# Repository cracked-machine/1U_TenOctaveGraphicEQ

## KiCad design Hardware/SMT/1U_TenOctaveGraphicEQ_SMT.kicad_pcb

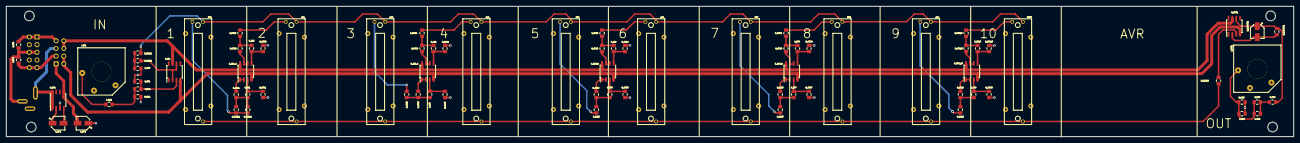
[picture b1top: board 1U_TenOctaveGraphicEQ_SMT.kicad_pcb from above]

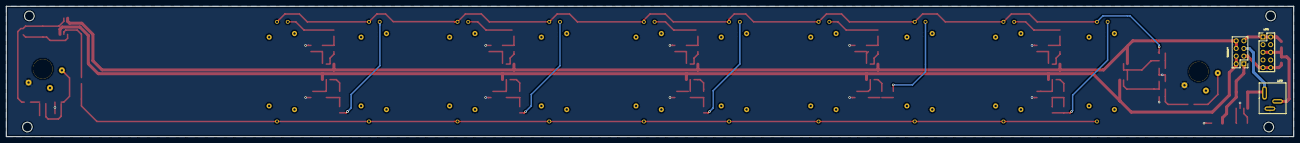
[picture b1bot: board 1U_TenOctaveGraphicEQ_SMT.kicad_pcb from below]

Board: 2 copper layers, 426.7 x 43.2 mm, 83 parts (3 on the bottom side), 62 nets.

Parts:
C_BP1, C_BP2: 100nF; C_0805_2012Metric_Pad1.15x1.40mm_HandSolder
C_BUFOUT1: 100uF; CP_Elec_4x5.4
C_CP1, C_CP2: 10uF; CP_Elec_4x5.4
C_DC1: 470nF; C_0805_2012Metric_Pad1.15x1.40mm_HandSolder
C_DC2, C_DC3: 1uF; C_0805_2012Metric_Pad1.15x1.40mm_HandSolder
C_GY1: 220nF; C_0805_2012Metric_Pad1.15x1.40mm_HandSolder
C_GY2: 100nF; C_0805_2012Metric_Pad1.15x1.40mm_HandSolder
C_GY3: 68nF; C_0805_2012Metric_Pad1.15x1.40mm_HandSolder
C_GY4: 33nF; C_0805_2012Metric_Pad1.15x1.40mm_HandSolder
C_GY5: 15nF; C_0805_2012Metric_Pad1.15x1.40mm_HandSolder
C_GY6: 10nF; C_0805_2012Metric_Pad1.15x1.40mm_HandSolder
C_GY7: 4.7nF; C_0805_2012Metric_Pad1.15x1.40mm_HandSolder
C_GY8: 2.2nF; C_0805_2012Metric_Pad1.15x1.40mm_HandSolder
C_GY9: 1nF; C_0805_2012Metric_Pad1.15x1.40mm_HandSolder
C_GY10: 680pF; C_0805_2012Metric_Pad1.15x1.40mm_HandSolder
C_PRE2: 1uF; C_0805_2012Metric_Pad1.15x1.40mm_HandSolder
C_PRE3: 390nF; C_0805_2012Metric_Pad1.15x1.40mm_HandSolder
C_PRE4: 220nF; C_0805_2012Metric_Pad1.15x1.40mm_HandSolder
C_PRE5: 100nF; C_0805_2012Metric_Pad1.15x1.40mm_HandSolder
C_PRE6: 47nF; C_0805_2012Metric_Pad1.15x1.40mm_HandSolder
C_PRE7: 22nF; C_0805_2012Metric_Pad1.15x1.40mm_HandSolder
C_PRE8: 10nF; C_0805_2012Metric_Pad1.15x1.40mm_HandSolder
C_PRE9: 6.8nF; C_0805_2012Metric_Pad1.15x1.40mm_HandSolder
C_PRE10: 3.3nF; C_0805_2012Metric_Pad1.15x1.40mm_HandSolder
C_PREA1: 680nF; C_0805_2012Metric_Pad1.15x1.40mm_HandSolder
C_PREB1: 820nF; C_0805_2012Metric_Pad1.15x1.40mm_HandSolder
C_RF1, C_RF2: 100pF; C_0805_2012Metric_Pad1.15x1.40mm_HandSolder
C_RF3: 1nF; C_0805_2012Metric_Pad1.15x1.40mm_HandSolder
J_IN1: AudioJack2_Ground_Switch; 112APCX
J_OUT1: AudioJack2_Ground_Switch; 112APCX
J_PS1: Conn_02x05_Odd_Even; PinHeader_2x05_P2.54mm_Vertical
J_PS2: Barrel_Jack; Wurth Elektronik Through Hole DC Power Socket WR-DC Series,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
J_PWRSEL1: Conn_02x04_Odd_Even; PinHeader_2x04_P2.54mm_Vertical
RV1, RV2, RV3, RV4, RV5, RV6, RV7, RV8, RV9, RV10: 10K; PTA2043
R_BEAD1, R_BEAD2: 10R; R_0805_2012Metric_Pad1.15x1.40mm_HandSolder
R_BUFOUT1: 2K7; R_0805_2012Metric_Pad1.15x1.40mm_HandSolder
R_GAIN1: 2K7; R_0805_2012Metric_Pad1.15x1.40mm_HandSolder
R_GYA1, R_GYA2, R_GYA3, R_GYA4, R_GYA5, R_GYA6, R_GYA7, R_GYA8, R_GYA9, R_GYA10: 680R; R_0805_2012Metric_Pad1.15x1.40mm_HandSolder
R_GYB1, R_GYB8: 110K; R_0805_2012Metric_Pad1.15x1.40mm_HandSolder
R_GYB2, R_GYB5: 100K; R_0805_2012Metric_Pad1.15x1.40mm_HandSolder
R_GYB3, R_GYB7: 91K; R_0805_2012Metric_Pad1.15x1.40mm_HandSolder
R_GYB4, R_GYB6, R_GYB9: 82K; R_0805_2012Metric_Pad1.15x1.40mm_HandSolder
R_GYB10: 62K; R_0805_2012Metric_Pad1.15x1.40mm_HandSolder
R_PD1: 100K; R_0805_2012Metric_Pad1.15x1.40mm_HandSolder
R_PD2: 1M; R_0805_2012Metric_Pad1.15x1.40mm_HandSolder
R_RF1: 1K; R_0805_2012Metric_Pad1.15x1.40mm_HandSolder
R_RF2: 470R; R_0805_2012Metric_Pad1.15x1.40mm_HandSolder
U_CP1: _TC7662B; SOIC-8_3.9x4.9mm_P1.27mm
U_GY1_2, U_GY3_4, U_GY5_6, U_GY7_8, U_GY9_10: TL072; SOIC-8_3.9x4.9mm_P1.27mm
U_IN1: TL071; SOIC-8_3.9x4.9mm_P1.27mm
U_OUT1: TL071; SOIC-8_3.9x4.9mm_P1.27mm

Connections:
/CP_V+: J_PS2.1, J_PWRSEL1.5, U_CP1.1, U_CP1.8
/CP_V-: C_CP2.2, J_PWRSEL1.1, U_CP1.5
/EURO_GND: C_BP1.2, C_BP2.1, J_PS1.5, J_PS1.6, J_PS2.3
/GND: C_CP2.1, C_RF1.2, C_RF2.2, C_RF3.2, J_IN1.S, J_OUT1.S, J_PS2.2, R_GYB1.2, R_GYB2.2, R_GYB3.2, R_GYB4.2, R_GYB5.2, R_GYB6.2, R_GYB7.2, R_GYB8.2, R_GYB9.2, R_GYB10.2, R_PD1.2, R_PD2.2, U_CP1.3
/PS_V+: C_BP1.1, J_PS1.1, J_PS1.2, J_PWRSEL1.7
/PS_V-: C_BP2.2, J_PS1.9, J_PS1.10, J_PWRSEL1.3
/SeriesResonatorBlock/EQ_IN: RV1.1, RV2.1, RV3.1, RV4.1, RV5.1, RV6.1, RV7.1, RV8.1, RV9.1, RV10.1, R_BEAD1.1
/SeriesResonatorBlock/EQ_OUT: RV1.3, RV2.3, RV3.3, RV4.3, RV5.3, RV6.3, RV7.3, RV8.3, RV9.3, RV10.3, R_BEAD2.2
/V+: J_PWRSEL1.6, J_PWRSEL1.8, U_GY1_2.8, U_GY3_4.8, U_GY5_6.8, U_GY7_8.8, U_GY9_10.8, U_IN1.7, U_OUT1.7
/V-: J_PWRSEL1.2, J_PWRSEL1.4, U_GY1_2.4, U_GY3_4.4, U_GY5_6.4, U_GY7_8.4, U_GY9_10.4, U_IN1.4, U_OUT1.4
unnamed: C_BUFOUT1.1, R_BUFOUT1.1, R_RF2.2, U_OUT1.6
unnamed: C_BUFOUT1.2, R_BUFOUT1.2, U_OUT1.2
unnamed: C_CP1.1, U_CP1.2
unnamed: C_CP1.2, U_CP1.4
unnamed: C_DC1.1, R_PD1.1, R_RF1.1
unnamed: C_DC1.2, J_IN1.T
unnamed: C_DC2.1, C_DC3.1, C_RF3.1, J_OUT1.T, R_PD2.1
unnamed: C_DC2.2, C_DC3.2, R_RF2.1
unnamed: C_GY1.1, C_PREA1.2, C_PREB1.2, R_GYA1.1
unnamed: C_GY1.2, R_GYB1.1, U_GY1_2.3
unnamed: C_GY2.1, C_PRE2.2, R_GYA2.1
unnamed: C_GY2.2, R_GYB2.1, U_GY1_2.5
unnamed: C_GY3.1, C_PRE3.2, R_GYA3.1
unnamed: C_GY3.2, R_GYB3.1, U_GY3_4.3
unnamed: C_GY4.1, C_PRE4.2, R_GYA4.1
unnamed: C_GY4.2, R_GYB4.1, U_GY3_4.5
unnamed: C_GY5.1, C_PRE5.2, R_GYA5.1
unnamed: C_GY5.2, R_GYB5.1, U_GY5_6.3
unnamed: C_GY6.1, C_PRE6.2, R_GYA6.1
unnamed: C_GY6.2, R_GYB6.1, U_GY5_6.5
unnamed: C_GY7.1, C_PRE7.2, R_GYA7.1
unnamed: C_GY7.2, R_GYB7.1, U_GY7_8.3
unnamed: C_GY8.1, C_PRE8.2, R_GYA8.1
unnamed: C_GY8.2, R_GYB8.1, U_GY7_8.5
unnamed: C_GY9.1, C_PRE9.2, R_GYA9.1
unnamed: C_GY9.2, R_GYB9.1, U_GY9_10.3
unnamed: C_GY10.1, C_PRE10.2, R_GYA10.1
unnamed: C_GY10.2, R_GYB10.1, U_GY9_10.5
unnamed: C_PRE2.1, RV2.2
unnamed: C_PRE3.1, RV3.2
unnamed: C_PRE4.1, RV4.2
unnamed: C_PRE5.1, RV5.2
unnamed: C_PRE6.1, RV6.2
unnamed: C_PRE7.1, RV7.2
unnamed: C_PRE8.1, RV8.2
unnamed: C_PRE9.1, RV9.2
unnamed: C_PRE10.1, RV10.2
unnamed: C_PREA1.1, C_PREB1.1, RV1.2
unnamed: C_RF1.1, R_RF1.2, U_IN1.3
unnamed: C_RF2.1, R_BEAD1.2, R_GAIN1.1
unnamed: R_BEAD2.1, U_OUT1.3
unnamed: R_GAIN1.2, U_IN1.2, U_IN1.6
unnamed: R_GYA1.2, U_GY1_2.1, U_GY1_2.2
unnamed: R_GYA2.2, U_GY1_2.6, U_GY1_2.7
unnamed: R_GYA3.2, U_GY3_4.1, U_GY3_4.2
unnamed: R_GYA4.2, U_GY3_4.6, U_GY3_4.7
unnamed: R_GYA5.2, U_GY5_6.1, U_GY5_6.2
unnamed: R_GYA6.2, U_GY5_6.6, U_GY5_6.7
unnamed: R_GYA7.2, U_GY7_8.1, U_GY7_8.2
unnamed: R_GYA8.2, U_GY7_8.6, U_GY7_8.7
unnamed: R_GYA9.2, U_GY9_10.1, U_GY9_10.2
unnamed: R_GYA10.2, U_GY9_10.6, U_GY9_10.7

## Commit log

2018-09-27 Completed Layout
2018-09-30 restructure
2019-05-27 generated schematic docs
